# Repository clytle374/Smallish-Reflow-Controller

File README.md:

# Smallish-Reflow-Controller

This code started as Tiny Reflow Controller and adapted and modified https://github.com/rocketscream/TinyReflowController  While some of the original code still exists like much of the display, it was more of a teaching tool for me at this point.

This runs on a ATmega644PA processor on a MightyCore board for development. So the MightyCore board library needs loaded to build with the Arduino IDE. It uses a 128x64 OLED display with the SSD1306 driver and MAX6675 thermocouple chip plus outputs for SSR(I also added a 4N35 opto), servo and buzzer.

Here is the basic setup of the reflow profiles.  There are 2 profiles one for lead and another for lead free, the parameters in this chart have separate entries for each profile.

This is a overview of the settings, more later on the oven and how the code works.  Preheat is set at 2C/s. If your oven cannot hold a 2C/s ramp, I am not sure this code will work out very well on your oven. The ramp will continue until the SOAK_TEMP_HOLDOFF is reached.  Its value is the number of degrees before the SOAK_TEMP. So if SOAK_TEMP is 150C and SOAK_TEMP_HOLDOFF is 25C then the elements will cut out at 125C. Temperature overshoot will come close to reaching the SOAK_TEMP. The SOAK_TIME will start when SOAK_TIMER_TEMP is reached. If the delta temp becomes too low during this the time the program will start adding small pulses of temperature increase, the display will show “RECOVER” at the bottom. There is an option for adding in a SOAK_RAMP to increase the temp linearly over the soak cycle, setting it to 0 disables it.

At the end of the soak cycle a 2C/s ramp is started.  Just like the SOAK_TEMP_HOLDOFF the heaters will cutoff at the value of REFLOW_TEMP_HOLDOFF before REFLOW_TEMP temp is reached. Once REFLOW_TIMER_TEMP is reached the timer will start and hold temperature until the set REFLOW_TIME is reached.

Why use those holdoff values?  I could not tune the PID of the system to not overshoot severely and hold a steady temperature. In researching this issue I found this quote “The unfortunate relationship between servo systems and oscillators is very apparent in thermal control systems.” by  Jim Williams

Results

Blue= Setpoint       Orange= Temperature        Red= Output %
You can see the recovery right before the oven hits reflow temp. Below is an example of the TEMP_HOLDOFF values being too large making the reflow cycle too long.

The oven is based on a $20 toaster oven from Walmart (MS54100112163), 2 of them actually as the whole oven is cheaper than one heating element. Each oven has a 470 watt and 580 watt quartz elements.  The oven was fitted with an insert made from the second oven and aluminum flashing as the top half of the chamber for less heat mass. It was insulated with Kaowool, and cheap aluminum coated fiberglass adhesive on the inside. The quarts tubes were cut shorter with a diamond wheel in a dreamil tool and all 4 were put in the bottom, giving about 2KW.  In hindsight I would have tried using aluminum flashing with koawool across the bottom/back/top before I cut the elements. 4 holes were drilled though the oven sides and into the chamber.  Sheet metal screws were then used as stay bolts to hold it in place.  One of the element shields was used at the bottom front to protect the glass due to their close proximity.  It might not be needed, but it greatly stiffens the chamber.

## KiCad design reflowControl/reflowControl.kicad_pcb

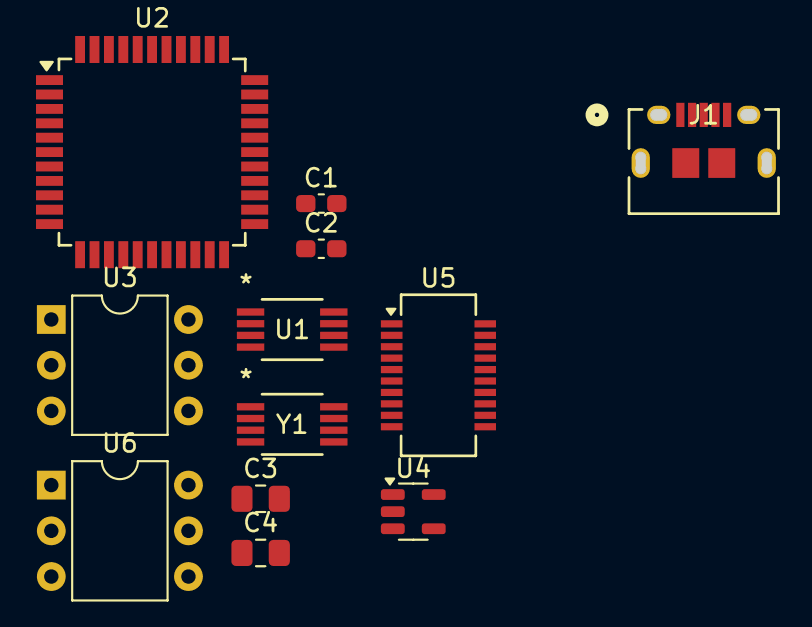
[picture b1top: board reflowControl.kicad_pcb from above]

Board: 2 copper layers, 12 parts (0 on the bottom side), 6 nets, no tracks yet.

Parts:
C1, C2: 1u; C_0603_1608Metric_Pad1.08x0.95mm_HandSolder
C3, C4: 22p; C_0805_2012Metric_Pad1.18x1.45mm_HandSolder
J1: 10118194-0001LF; CONN_10118194-0001LF_AMP
U1: MAX6675ISA+; 21-0041B_8_MXM-M
U2: ATmega644PA-A; TQFP-44_10x10mm_P0.8mm
U3, U6: 4N35; DIP-6_W7.62mm
U4: MIC5317-3.3xM5; SOT-23-5
U5: FT231XS; SSOP-20_3.9x8.7mm_P0.635mm
Y1: Crystal; 21-0041B_8_MXM-M

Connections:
GND: C1.2, C2.2, C3.2, C4.2, U2.6 (GND), U2.18 (GND), U2.28 (GND), U2.39 (GND), U3.2, U4.2 (GND)
unnamed: U2.5 (VCC), U2.17 (VCC), U2.38 (VCC)
unnamed: C3.1, U2.8 (XTAL1), Y1.1
unnamed: C4.1, U2.7 (XTAL2), Y1.2
unnamed: C1.1, U4.1 (VIN), U4.3 (EN)
unnamed: C2.1, U4.5 (VOUT)

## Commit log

2024-04-23 arduino code added
2024-04-23 fixed git in subfolder
2024-04-23 V31 organize and comment code
2024-04-23 V32 fixing menus, still some bugs
2024-04-23 V33 fixed menus, tweeks, mode select knob improved
2024-04-23 V34 fixing menus still, eeprom fixed, code cleanup
2024-04-23 V35 cleanup, random bugs, bedtime
2024-04-23 V35.2 readme, cleanup, random bugs, bedtime
2024-04-23 V35.3 readme, cleanup, random bugs, bedtime
2024-04-23 V35.4 readme, cleanup, random bugs, bedtime
2024-04-23 V35.5 readme, images, cleanup, random bugs, bedtime
2024-04-24 V36 cleanup, removed hardcoded values, unpate readme
2024-04-24 update readme, images
2024-04-25 starting PCB
2024-04-26 added delta C,fixed overshoot issue in coast function, PCB parts,
2024-04-26 V38 improved code as memory was low, soak caost is fixed
2024-04-26 new parameters to chart
2024-04-26 new image
2024-04-27 parameter updating, saving while it kinda works
2024-04-27 new parameters, removed hardcoded stuff, tried to improve code quality
2024-04-27 finally got .h file to work to unmess the program a little
2024-04-28 fixed bug with delta T, played with formatting display
2024-04-28 display changed, recovery changed, pics and docs modified
2024-04-29 fixed where the timer start setpoints could be lower than setpoint, display picture
2024-04-30 schematic work
2024-05-15 test
